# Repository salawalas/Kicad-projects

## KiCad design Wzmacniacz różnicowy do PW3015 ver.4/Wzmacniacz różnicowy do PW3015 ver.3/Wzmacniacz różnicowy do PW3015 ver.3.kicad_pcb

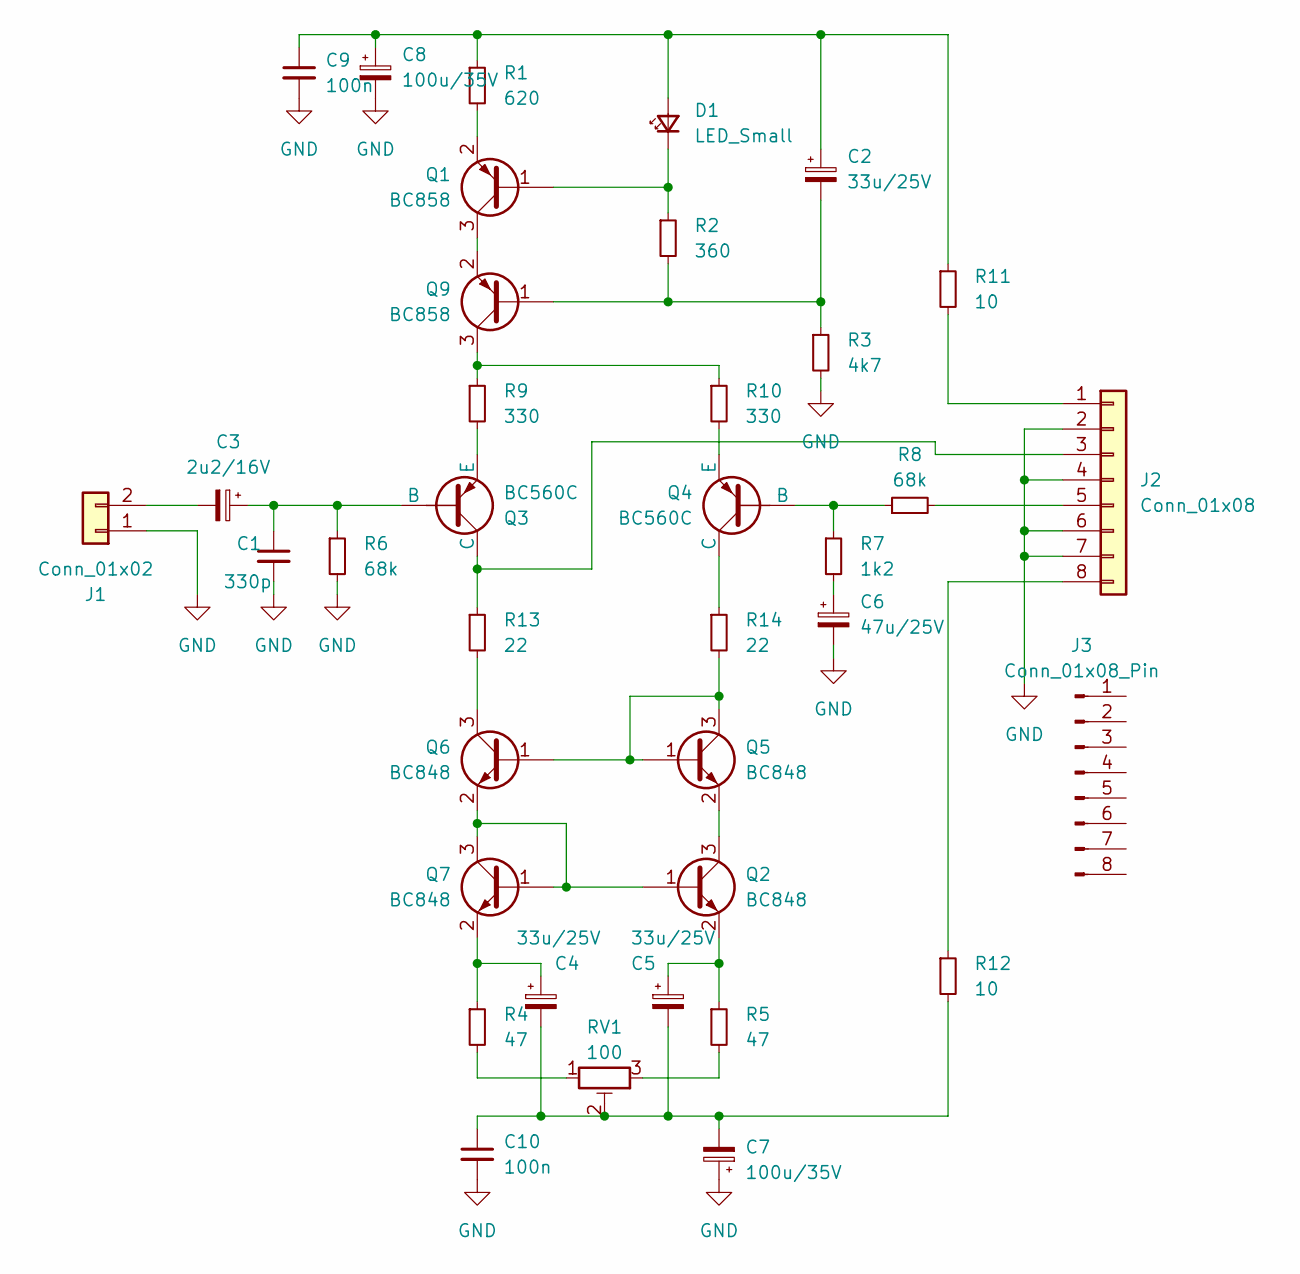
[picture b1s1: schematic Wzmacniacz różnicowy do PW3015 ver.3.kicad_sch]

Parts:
C1: 330p; C_Axial_L3.8mm_D2.6mm_P7.50mm_Horizontal
C2, C4, C5: 33u/25V; CP_Radial_Tantal_D5.5mm_P5.00mm
C3: 2u2/16V; CP_Radial_D5.0mm_P2.50mm
C6: 47u/25V; CP_Radial_D5.0mm_P2.50mm
C7, C8: 100u/35V; CP_Radial_D8.0mm_P5.00mm
C9, C10: 100n; C_0805_2012Metric_Pad1.18x1.45mm_HandSolder
D1: LED_Small; LED_D5.0mm
J1: Conn_01x02; JST_PH_B2B-PH-K_1x02_P2.00mm_Vertical
J2: Conn_01x08; PinHeader_1x08_P2.54mm_Horizontal
J3: Conn_01x08_Pin; PinHeader_1x08_P2.54mm_Vertical
Q1, Q9: BC858; SOT-23
Q2, Q5, Q6, Q7: BC848; SOT-23
Q3, Q4: BC560C; TO-92_Wide
R1: 620; R_1206_3216Metric_Pad1.30x1.75mm_HandSolder
R2: 360; R_1206_3216Metric_Pad1.30x1.75mm_HandSolder
R3: 4k7; R_1206_3216Metric_Pad1.30x1.75mm_HandSolder
R4, R5: 47; R_1206_3216Metric_Pad1.30x1.75mm_HandSolder
R6, R8: 68k; R_1206_3216Metric_Pad1.30x1.75mm_HandSolder
R7: 1k2; R_1206_3216Metric_Pad1.30x1.75mm_HandSolder
R9, R10: 330; R_1206_3216Metric_Pad1.30x1.75mm_HandSolder
R11, R12: 10; R_1206_3216Metric_Pad1.30x1.75mm_HandSolder
R13, R14: 22; R_1206_3216Metric_Pad1.30x1.75mm_HandSolder
RV1: 100; Potentiometer_Bourns_3296X_Horizontal

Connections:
GND: C1.2, C6.2, C7.1, C8.2, C9.2, C10.2, J1.1, J2.2, J2.4, J2.6, J2.7, R3.2, R6.2
unnamed: C6.1, R7.2
unnamed: C4.2, C5.2, C7.2, C10.1, R12.2, RV1.2
unnamed: C2.1, C8.1, C9.1, D1.2 (A), R1.1, R11.1
unnamed: D1.1 (K), Q1.1 (B), R2.1
unnamed: C3.2, J1.2
unnamed: J2.1, R11.2
unnamed: J2.3, Q3.1 (C), R13.1
unnamed: J2.5, R8.2
unnamed: J2.8, R12.1
unnamed: Q1.3 (C), Q9.2 (E)
unnamed: Q1.2 (E), R1.2
unnamed: Q2.1 (B), Q6.2 (E), Q7.1 (B), Q7.3 (C)
unnamed: Q2.3 (C), Q5.2 (E)
unnamed: C5.1, Q2.2 (E), R5.1
unnamed: C1.1, C3.1, Q3.2 (B), R6.1
unnamed: Q3.3 (E), R9.2
unnamed: Q4.2 (B), R7.1, R8.1
unnamed: Q4.1 (C), R14.1
unnamed: Q4.3 (E), R10.2
unnamed: Q5.1 (B), Q5.3 (C), Q6.1 (B), R14.2
unnamed: Q6.3 (C), R13.2
unnamed: C4.1, Q7.2 (E), R4.1
unnamed: C2.2, Q9.1 (B), R2.2, R3.1
unnamed: Q9.3 (C), R9.1, R10.1
unnamed: R4.2, RV1.1
unnamed: R5.2, RV1.3

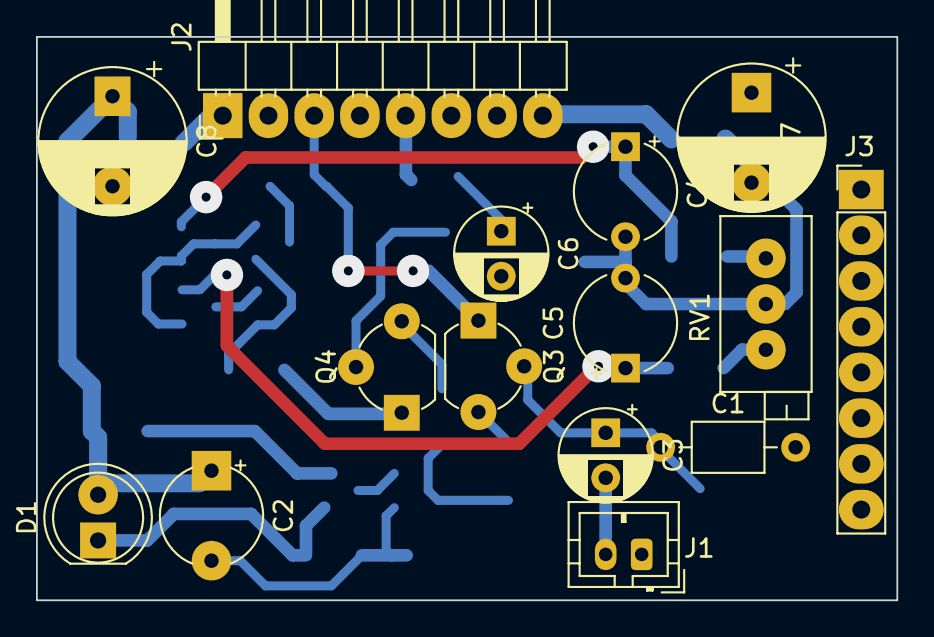
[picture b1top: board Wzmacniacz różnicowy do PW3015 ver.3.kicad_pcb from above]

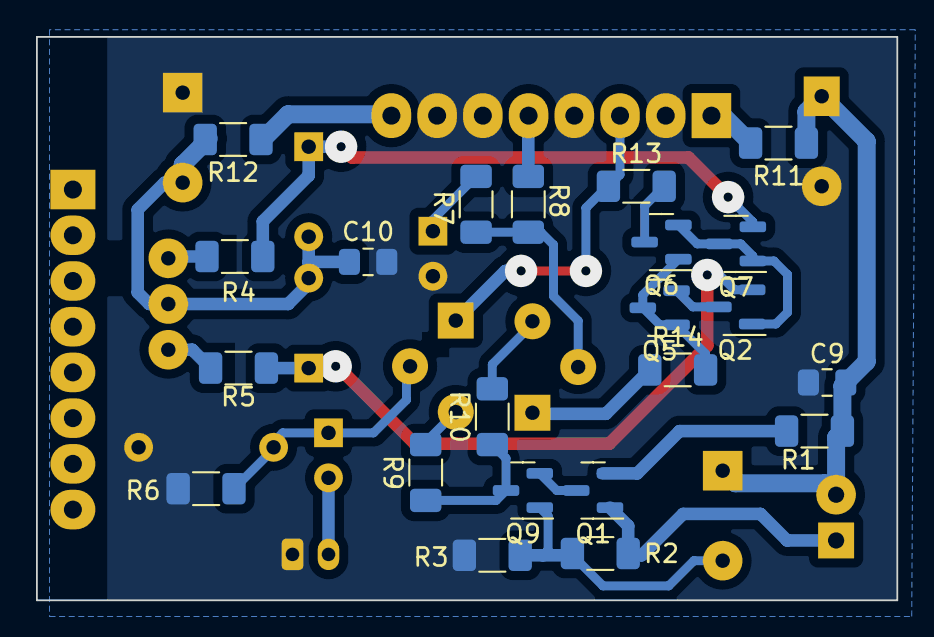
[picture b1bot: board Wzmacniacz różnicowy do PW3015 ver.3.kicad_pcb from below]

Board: 2 copper layers, 47.8 x 31.3 mm, 37 parts (22 on the bottom side), 27 nets.

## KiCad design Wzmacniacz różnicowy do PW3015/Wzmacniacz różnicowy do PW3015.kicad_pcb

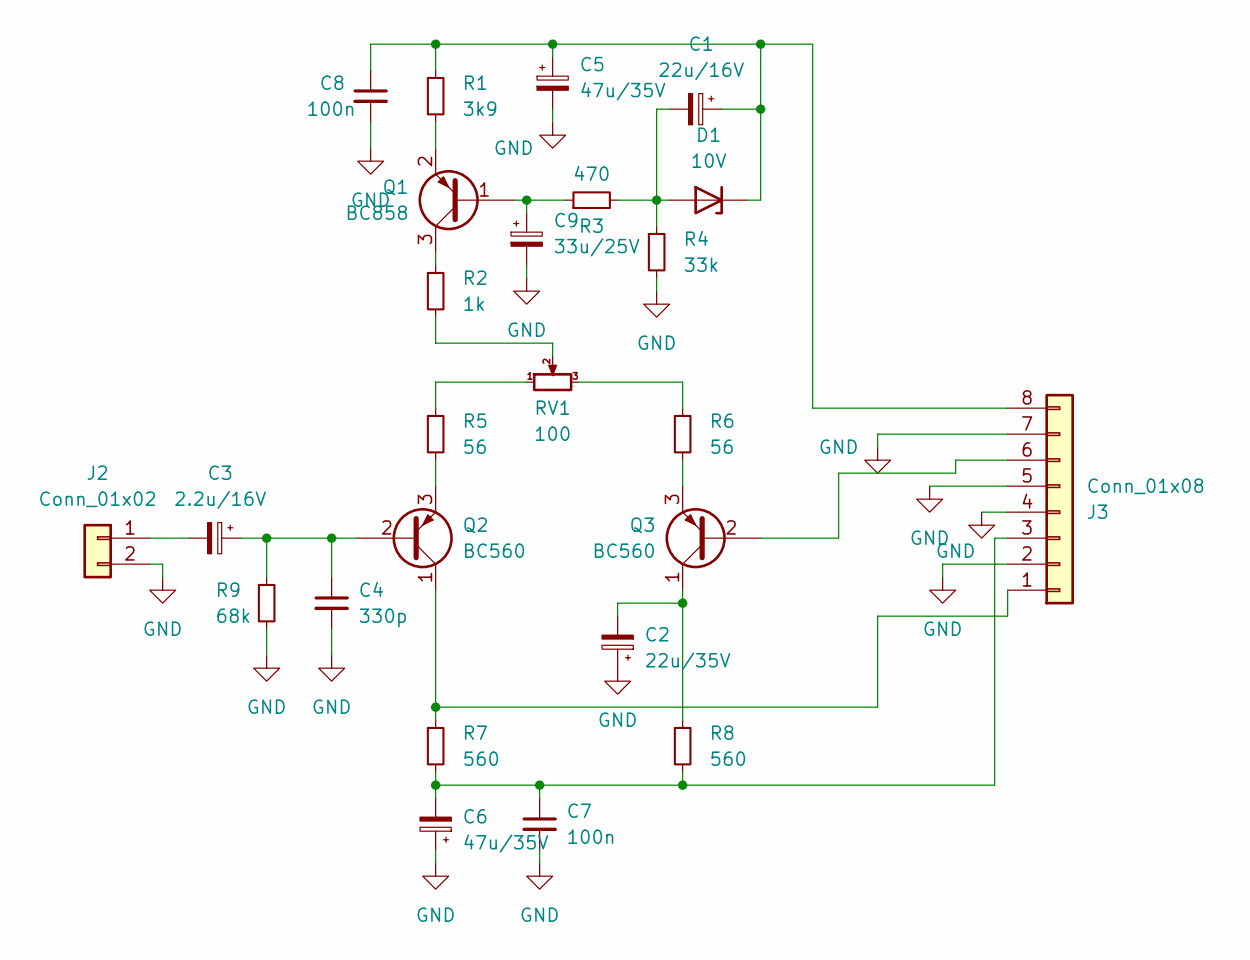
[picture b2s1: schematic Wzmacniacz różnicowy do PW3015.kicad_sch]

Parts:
C1: 22u/16V; CP_Radial_D5.0mm_P2.50mm
C2: 22u/35V; CP_Radial_D8.0mm_P3.80mm
C3: 2.2u/16V; CP_Radial_D5.0mm_P2.50mm
C4: 330p; C_Disc_D4.3mm_W1.9mm_P5.00mm
C5, C6: 47u/35V; CP_Radial_D10.0mm_P3.50mm
C7, C8: 100n; C_0805_2012Metric_Pad1.18x1.45mm_HandSolder
C9: 33u/25V; CP_Radial_Tantal_D5.5mm_P5.00mm
D1: 10V; D_T-1_P5.08mm_Horizontal
J2: Conn_01x02; JST_EH_B2B-EH-A_1x02_P2.50mm_Vertical
J3: Conn_01x08; PinHeader_1x08_P2.54mm_Horizontal
Q1: BC858; SOT-23
Q2, Q3: BC560; TO-92L_Wide
R1: 3k9; R_1206_3216Metric_Pad1.30x1.75mm_HandSolder
R2: 1k; R_1206_3216Metric_Pad1.30x1.75mm_HandSolder
R3: 470; R_1206_3216Metric_Pad1.30x1.75mm_HandSolder
R4: 33k; R_1206_3216Metric_Pad1.30x1.75mm_HandSolder
R5, R6: 56; R_1206_3216Metric_Pad1.30x1.75mm_HandSolder
R7, R8: 560; R_1206_3216Metric_Pad1.30x1.75mm_HandSolder
R9: 68k; R_1206_3216Metric_Pad1.30x1.75mm_HandSolder
RV1: 100; Potentiometer_Bourns_3296W_Vertical

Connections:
GND: C2.1, C4.2, C5.2, C6.1, C7.2, C8.2, C9.2, J2.2, J3.2, J3.4, J3.5, J3.7, R4.2, R9.2
unnamed: C1.2, D1.2 (A), R3.2, R4.1
unnamed: C1.1, C5.1, C8.1, D1.1 (K), J3.8, R1.1
unnamed: C3.2, J2.1
unnamed: J3.1, Q2.1 (C), R7.1
unnamed: C6.2, C7.1, J3.3, R7.2, R8.2
unnamed: J3.6, Q3.2 (B)
unnamed: C9.1, Q1.1 (B), R3.1
unnamed: Q1.3 (C), R2.1
unnamed: Q1.2 (E), R1.2
unnamed: C3.1, C4.1, Q2.2 (B), R9.1
unnamed: Q2.3 (E), R5.2
unnamed: C2.2, Q3.1 (C), R8.1
unnamed: Q3.3 (E), R6.2
unnamed: R2.2, RV1.2
unnamed: R5.1, RV1.1
unnamed: R6.1, RV1.3

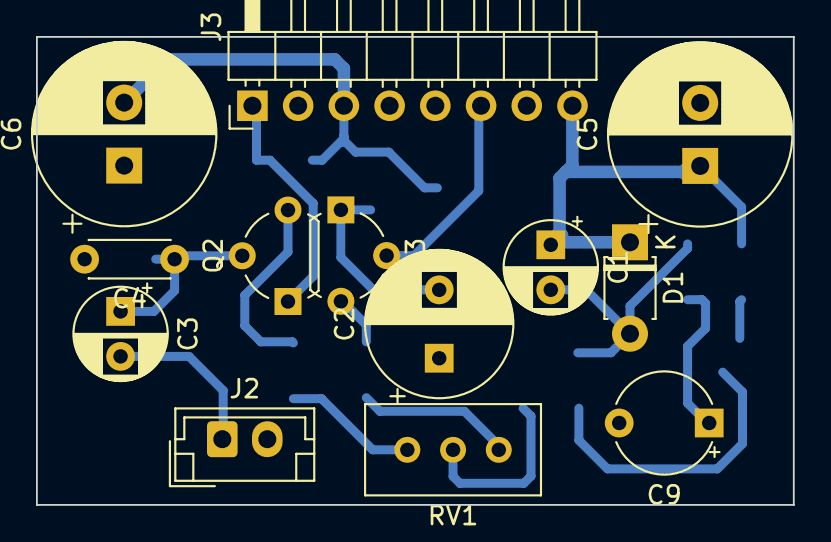
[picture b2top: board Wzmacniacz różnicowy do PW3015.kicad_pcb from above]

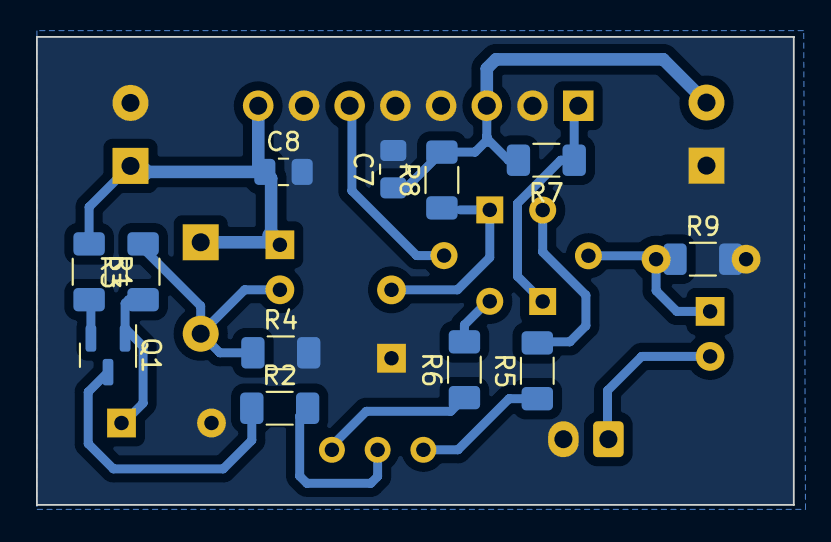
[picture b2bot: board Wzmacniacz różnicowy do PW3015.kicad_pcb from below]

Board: 2 copper layers, 42.1 x 26.0 mm, 25 parts (12 on the bottom side), 17 nets.

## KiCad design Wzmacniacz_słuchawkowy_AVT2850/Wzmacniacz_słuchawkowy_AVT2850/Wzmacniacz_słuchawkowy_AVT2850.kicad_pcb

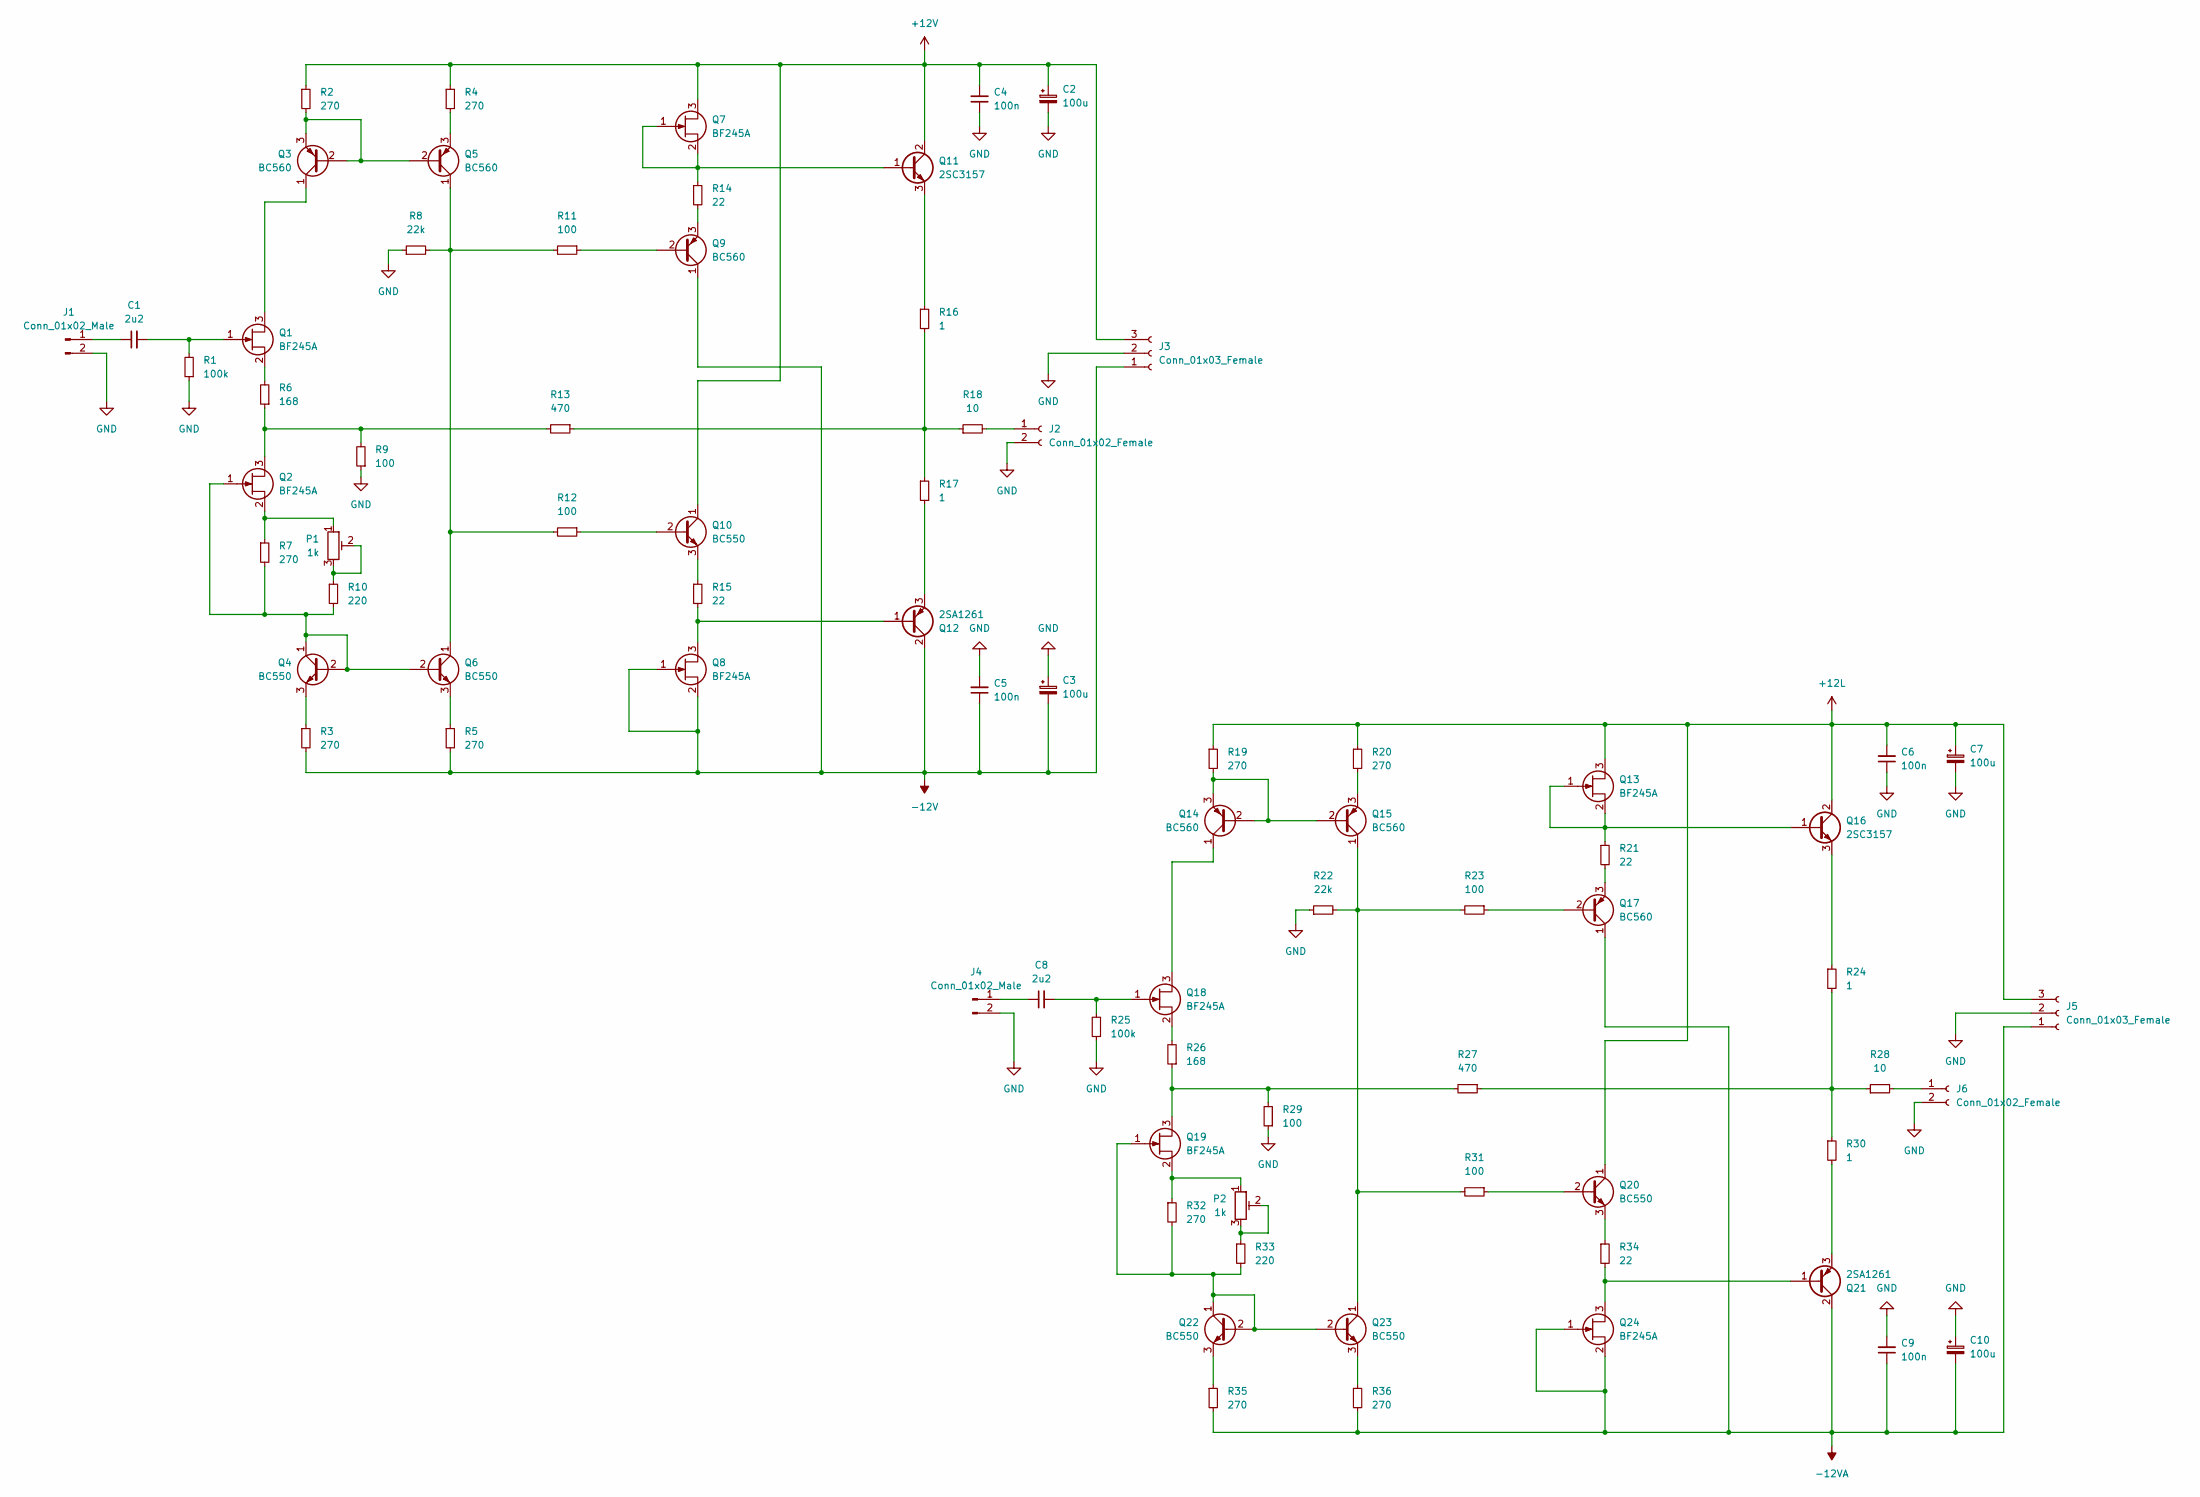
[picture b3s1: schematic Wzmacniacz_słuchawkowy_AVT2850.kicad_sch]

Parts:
C1, C8: 2u2; C_Rect_L11.0mm_W5.1mm_P10.00mm_MKT
C2, C3, C7, C10: 100u; CP_Radial_D8.0mm_P3.50mm
C4, C5, C6, C9: 100n; C_Axial_L3.8mm_D2.6mm_P10.00mm_Horizontal
J1, J4: Conn_01x02_Male; JST_EH_S2B-EH_1x02_P2.50mm_Horizontal
J2, J6: Conn_01x02_Female; JST_EH_B2B-EH-A_1x02_P2.50mm_Vertical
J3, J5: Conn_01x03_Female; JST_EH_S3B-EH_1x03_P2.50mm_Horizontal
P1, P2: 1k; Potentiometer_Bourns_3266Y_Vertical
Q1, Q2, Q7, Q8, Q13, Q18, Q19, Q24: BF245A; TO-92
Q3, Q5, Q9, Q14, Q15, Q17: BC560; TO-92
Q4, Q6, Q10, Q20, Q22, Q23: BC550; TO-92
Q11, Q16: 2SC3157; TO-220-3_Vertical
Q12, Q21: 2SA1261; TO-220-3_Vertical
R1, R25: 100k; R_Axial_DIN0207_L6.3mm_D2.5mm_P10.16mm_Horizontal
R2, R3, R4, R5, R7, R19, R20, R32, R35, R36: 270; R_Axial_DIN0207_L6.3mm_D2.5mm_P10.16mm_Horizontal
R6, R26: 168; R_Axial_DIN0207_L6.3mm_D2.5mm_P10.16mm_Horizontal
R8, R22: 22k; R_Axial_DIN0207_L6.3mm_D2.5mm_P10.16mm_Horizontal
R9, R11, R12, R23, R29, R31: 100; R_Axial_DIN0207_L6.3mm_D2.5mm_P10.16mm_Horizontal
R10, R33: 220; R_Axial_DIN0207_L6.3mm_D2.5mm_P10.16mm_Horizontal
R13, R27: 470; R_Axial_DIN0207_L6.3mm_D2.5mm_P10.16mm_Horizontal
R14, R15, R21, R34: 22; R_Axial_DIN0207_L6.3mm_D2.5mm_P10.16mm_Horizontal
R16, R17, R24, R30: 1; R_Axial_DIN0207_L6.3mm_D2.5mm_P10.16mm_Horizontal
R18, R28: 10; R_Axial_DIN0207_L6.3mm_D2.5mm_P10.16mm_Horizontal

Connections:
+12L: C6.2, C7.1, J5.3, Q13.3 (D), Q16.2 (C), Q20.1 (C), R19.1, R20.1
+12V: C2.1, C4.2, J3.3, Q7.3 (D), Q10.1 (C), Q11.2 (C), R2.1, R4.1
-12V: C3.2, C5.1, J3.1, Q8.1 (G), Q8.2 (S), Q9.1 (C), Q12.2 (C), R3.2, R5.2
-12VA: C9.1, C10.2, J5.1, Q17.1 (C), Q21.2 (C), Q24.1 (G), Q24.2 (S), R35.2, R36.2
GND: C2.2, C3.1, C4.1, C5.2, C6.1, C7.2, C9.2, C10.1, J1.2, J2.2, J3.2, J4.2, J5.2, J6.2, R1.1, R8.1, R9.1, R22.1, R25.1, R29.1
unnamed: C1.1, J1.1
unnamed: C1.2, Q1.1 (G), R1.2
unnamed: C8.1, J4.1
unnamed: C8.2, Q18.1 (G), R25.2
unnamed: J2.1, R18.2
unnamed: J6.1, R28.2
unnamed: P1.1, Q2.2 (S), R7.1
unnamed: P1.2, P1.3, R10.1
unnamed: P2.1, Q19.2 (S), R32.1
unnamed: P2.2, P2.3, R33.1
unnamed: Q1.2 (S), R6.2
unnamed: Q1.3 (D), Q3.1 (C)
unnamed: Q2.1 (G), Q4.1 (C), Q4.2 (B), Q6.2 (B), R7.2, R10.2
unnamed: Q2.3 (D), R6.1, R9.2, R13.2
unnamed: Q3.2 (B), Q3.3 (E), Q5.2 (B), R2.2
unnamed: Q4.3 (E), R3.1
unnamed: Q5.1 (C), Q6.1 (C), R8.2, R11.2, R12.2
unnamed: Q5.3 (E), R4.2
unnamed: Q6.3 (E), R5.1
unnamed: Q9.2 (B), R11.1
unnamed: Q9.3 (E), R14.2
unnamed: Q10.2 (B), R12.1
unnamed: Q10.3 (E), R15.1
unnamed: Q7.1 (G), Q7.2 (S), Q11.1 (B), R14.1
unnamed: Q11.3 (E), R16.1
unnamed: Q8.3 (D), Q12.1 (B), R15.2
unnamed: Q12.3 (E), R17.2
unnamed: Q13.1 (G), Q13.2 (S), Q16.1 (B), R21.1
unnamed: Q14.1 (C), Q18.3 (D)
unnamed: Q14.2 (B), Q14.3 (E), Q15.2 (B), R19.2
unnamed: Q15.1 (C), Q23.1 (C), R22.2, R23.2, R31.2
unnamed: Q15.3 (E), R20.2
unnamed: Q16.3 (E), R24.1
unnamed: Q17.2 (B), R23.1
unnamed: Q17.3 (E), R21.2
unnamed: Q18.2 (S), R26.2
unnamed: Q19.1 (G), Q22.1 (C), Q22.2 (B), Q23.2 (B), R32.2, R33.2
unnamed: Q19.3 (D), R26.1, R27.2, R29.2
unnamed: Q20.2 (B), R31.1
unnamed: Q20.3 (E), R34.1
unnamed: Q21.1 (B), Q24.3 (D), R34.2
unnamed: Q21.3 (E), R30.2
unnamed: Q22.3 (E), R35.1
unnamed: Q23.3 (E), R36.1
unnamed: R13.1, R16.2, R17.1, R18.1
unnamed: R24.2, R27.1, R28.1, R30.1

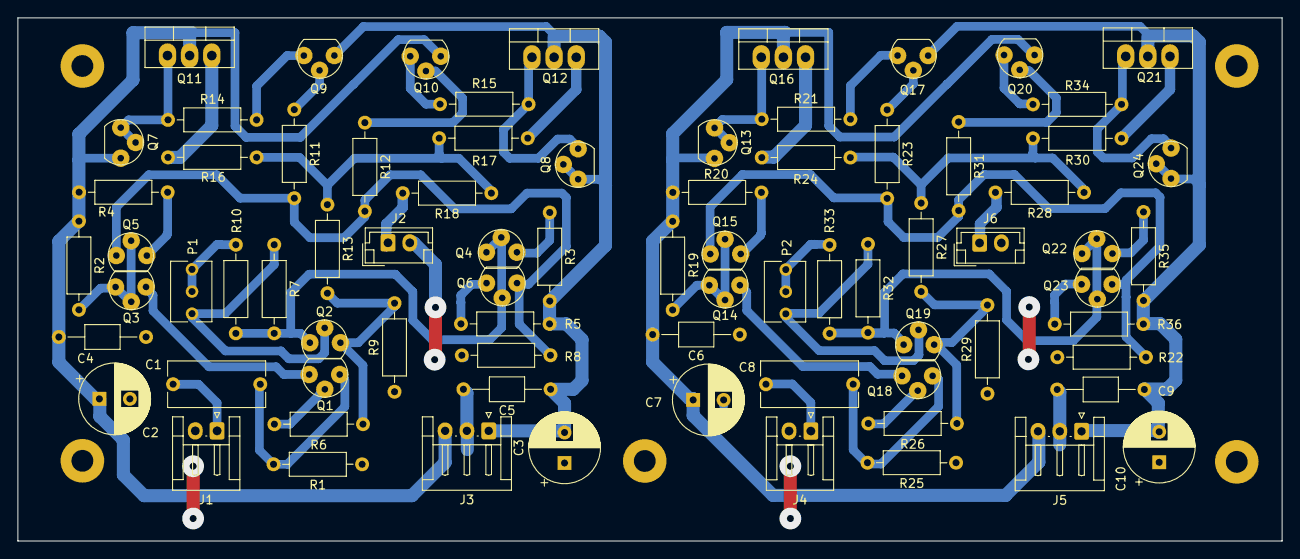
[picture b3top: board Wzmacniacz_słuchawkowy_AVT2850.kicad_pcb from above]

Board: 2 copper layers, 145.0 x 60.0 mm, 78 parts (0 on the bottom side), 51 nets.

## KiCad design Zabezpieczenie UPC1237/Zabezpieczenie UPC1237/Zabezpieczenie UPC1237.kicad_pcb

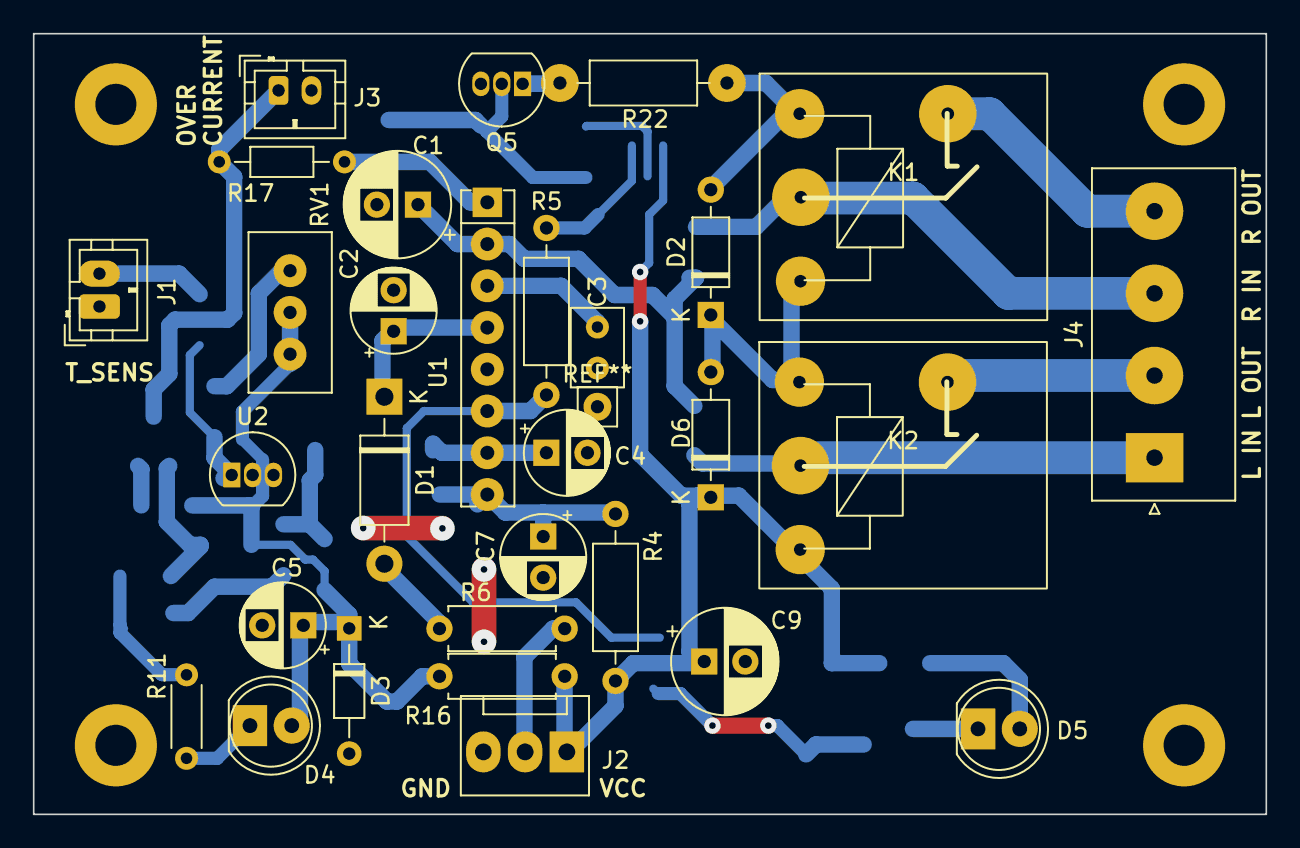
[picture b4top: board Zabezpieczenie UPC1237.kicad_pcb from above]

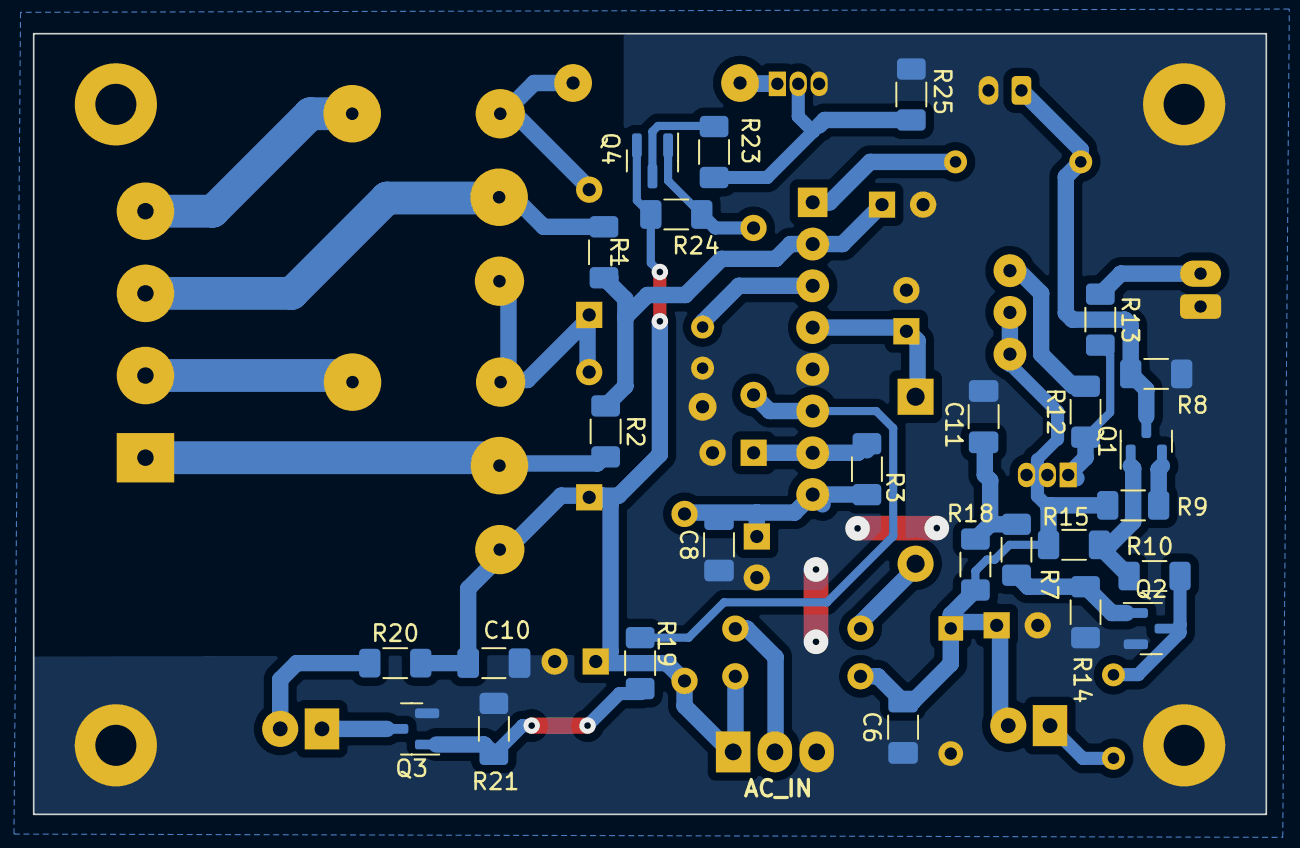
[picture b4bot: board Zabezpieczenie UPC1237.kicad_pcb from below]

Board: 2 copper layers, 75.0 x 47.5 mm, 56 parts (26 on the bottom side), 35 nets.

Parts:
C1: 330u/10/16V; CP_Radial_D6.3mm_P2.50mm
C2, C4: 4.7u/10/16V; CP_Radial_D5.0mm_P2.50mm
C3: 22n; C_Rect_L4.6mm_W3.0mm_P2.50mm_MKS02_FKP02
C5: 47u/16V; CP_Radial_D5.0mm_P2.50mm
C6, C8, C10, C11: 0.1u; C_1206_3216Metric_Pad1.33x1.80mm_HandSolder
C7: 47u/10/16; CP_Radial_D5.0mm_P2.50mm
C9: 100u/40V; CP_Radial_D6.3mm_P2.50mm
D1: 1N4007; D_DO-41_SOD81_P10.16mm_Horizontal
D2, D6: 1N4148; D_DO-35_SOD27_P7.62mm_Horizontal
D3: 12V; D_DO-34_SOD68_P7.62mm_Horizontal
D4, D5: LED_Small; LED_D5.0mm
J1, J3: Conn_01x02; JST_PH_B2B-PH-K_1x02_P2.00mm_Vertical
J2: Conn_01x03; FanPinHeader_1x03_P2.54mm_Vertical
J4: Conn_01x04_Pin; JST_NV_B04P-NV_1x04_P5.00mm_Vertical
K1, K2: Relay_SPST-NO; Relay_Hongfa_HF3FF
Q1, Q4: BC858; SOT-23
Q2, Q3: BC847; SOT-23
Q5: BC337; TO-92_Inline
R1, R2, R3: 56k; R_1206_3216Metric_Pad1.30x1.75mm_HandSolder
R4: 9k1; R_Axial_DIN0207_L6.3mm_D2.5mm_P10.16mm_Horizontal
R5: 47k; R_Axial_DIN0207_L6.3mm_D2.5mm_P10.16mm_Horizontal
R6: 12k; R_Axial_DIN0207_L6.3mm_D2.5mm_P7.62mm_Horizontal
R7, R14, R15: 4k7; R_1206_3216Metric_Pad1.30x1.75mm_HandSolder
R8: 2k7; R_1206_3216Metric_Pad1.30x1.75mm_HandSolder
R9: 3k9; R_1206_3216Metric_Pad1.30x1.75mm_HandSolder
R10: 1k; R_1206_3216Metric_Pad1.30x1.75mm_HandSolder
R11: 4k7; R_Axial_DIN0204_L3.6mm_D1.6mm_P5.08mm_Horizontal
R12: 3k; R_1206_3216Metric_Pad1.30x1.75mm_HandSolder
R13: 200; R_1206_3216Metric_Pad1.30x1.75mm_HandSolder
R16: 2k; R_Axial_DIN0207_L6.3mm_D2.5mm_P7.62mm_Horizontal
R17: 27k; R_Axial_DIN0204_L3.6mm_D1.6mm_P7.62mm_Horizontal
R18: 6k8; R_1206_3216Metric_Pad1.30x1.75mm_HandSolder
R19, R21, R23, R24, R25: 47k; R_1206_3216Metric_Pad1.30x1.75mm_HandSolder
R20: 10k; R_1206_3216Metric_Pad1.30x1.75mm_HandSolder
R22: 56; R_Axial_DIN0207_L6.3mm_D2.5mm_P10.16mm_Horizontal
RV1: 2k; Potentiometer_Bourns_3296W_Vertical
U1: UP1237; SIP-8_19x3mm_P2.54mm
U2: TL431LP; TO-92_Inline

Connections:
/INPUT_AC: J2.2, R6.1
/INPUT_L: J4.1, K2.13, R2.2
/INPUT_R: J4.3, K1.13, R1.2
/OUPUT_L: J4.2, K2.14
/OUPUT_R: J4.4, K1.14
/OVERLOAD_DET: R17.1, U1.1 (Overload_Detector)
/VCC: C9.1, C10.2, D6.1 (K), J2.1, K2.A2, Q4.2 (E), R4.1, R16.1, R20.2, R24.2
GND: C1.2, C2.2, C3.2, C4.2, C5.2, C6.2, C7.2, C8.1, C9.2, C10.1, C11.2, D3.2 (A), J1.1, J2.3, J3.2, Q2.2 (E), Q3.2 (E), Q5.3 (E), R8.1, R14.1, R21.1, R25.2, U1.5 (GND), U2.2 (A)
unnamed: D1.2 (A), R6.2
unnamed: C2.1, D1.1 (K), U1.4 (AC_OFF_Detector)
unnamed: D2.2 (A), K1.A1, R22.2
unnamed: D2.1 (K), D6.2 (A), K1.A2, K2.A1
unnamed: C5.1, C6.1, D3.1 (K), D4.2 (A), R9.2, R15.2, R16.2, R18.1, RV1.2, RV1.3
unnamed: D4.1 (K), R11.2
unnamed: D5.2 (A), R20.1
unnamed: D5.1 (K), Q3.3 (C)
unnamed: J1.2, R13.1
unnamed: J3.1, Q1.3 (C), R8.2, R17.2
unnamed: Q1.1 (B), R10.2, R15.1
unnamed: Q1.2 (E), R9.1
unnamed: Q2.1 (B), R7.2, R14.2
unnamed: Q2.3 (C), R10.1, R11.1
unnamed: Q3.1 (B), R19.2, R21.2
unnamed: Q4.1 (B), R5.2, R24.1
unnamed: Q4.3 (C), R23.2
unnamed: Q5.2 (B), R23.1, R25.1
unnamed: Q5.1 (C), R22.1
unnamed: R12.2, RV1.1
unnamed: C7.1, C8.2, R3.2, R4.2, U1.8 (+VCC)
unnamed: C3.1, U1.3 (Latch/Automat_Reset)
unnamed: C1.1, R1.1, R2.1, U1.2 (Output_Offset_Det.)
unnamed: R5.1, R19.1, U1.6 (Output_Relay_Driver)
unnamed: C4.1, R3.1, U1.7 (VCC_ON_Mute)
unnamed: C11.1, R7.1, R18.2, U2.3 (K)
unnamed: R12.1, R13.2, U2.1 (REF)

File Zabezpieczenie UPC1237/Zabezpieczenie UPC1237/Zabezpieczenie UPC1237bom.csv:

Reference;Value;Footprint
C1;330u/10/16V;Capacitor_THT:CP_Radial_D6.3mm_P2.50mm
C2 C4;4.7u/10/16V;Capacitor_THT:CP_Radial_D5.0mm_P2.50mm
C3;22n;Capacitor_THT:C_Rect_L4.6mm_W3.0mm_P2.50mm_MKS02_FKP02
C5;47u/16V;Capacitor_THT:CP_Radial_D5.0mm_P2.50mm
C6 C8 C10 C11;0.1u;Capacitor_SMD:C_1206_3216Metric_Pad1.33x1.80mm_HandSolder
C7;47u/10/16;Capacitor_THT:CP_Radial_D5.0mm_P2.50mm
C9;100u/40V;Capacitor_THT:CP_Radial_D6.3mm_P2.50mm
D1;1N4007;Diode_THT:D_DO-41_SOD81_P10.16mm_Horizontal
D2 D6;1N4148;Diode_THT:D_DO-35_SOD27_P7.62mm_Horizontal
D3;12V;Diode_THT:D_DO-34_SOD68_P7.62mm_Horizontal
D4 D5;LED_Small;LED_THT:LED_D5.0mm
J1 J3;Conn_01x02;Connector_JST:JST_PH_B2B-PH-K_1x02_P2.00mm_Vertical
J2;Conn_01x03;Connector:FanPinHeader_1x03_P2.54mm_Vertical
J4;Conn_01x04_Pin;Connector_JST:JST_NV_B04P-NV_1x04_P5.00mm_Vertical
K1 K2;Relay_SPST-NO;Relay:Relay_Hongfa_HF3FF
Q1 Q4;BC858;Package_TO_SOT_SMD:SOT-23
Q2 Q3;BC847;Package_TO_SOT_SMD:SOT-23
Q5;BC337;Package_TO_SOT_THT:TO-92_Inline
R1 R2 R3;56k;Resistor_SMD:R_1206_3216Metric_Pad1.30x1.75mm_HandSolder
R4;9k1;Resistor_THT:R_Axial_DIN0207_L6.3mm_D2.5mm_P10.16mm_Horizontal
R5;47k;Resistor_THT:R_Axial_DIN0207_L6.3mm_D2.5mm_P10.16mm_Horizontal
R6;12k;Resistor_THT:R_Axial_DIN0207_L6.3mm_D2.5mm_P7.62mm_Horizontal
R7 R14 R15;4k7;Resistor_SMD:R_1206_3216Metric_Pad1.30x1.75mm_HandSolder
R8;2k7;Resistor_SMD:R_1206_3216Metric_Pad1.30x1.75mm_HandSolder
R9;3k9;Resistor_SMD:R_1206_3216Metric_Pad1.30x1.75mm_HandSolder
R10;1k;Resistor_SMD:R_1206_3216Metric_Pad1.30x1.75mm_HandSolder
R11;4k7;Resistor_THT:R_Axial_DIN0204_L3.6mm_D1.6mm_P5.08mm_Horizontal
R12;3k;Resistor_SMD:R_1206_3216Metric_Pad1.30x1.75mm_HandSolder
R13;200;Resistor_SMD:R_1206_3216Metric_Pad1.30x1.75mm_HandSolder
R16;2k;Resistor_THT:R_Axial_DIN0207_L6.3mm_D2.5mm_P7.62mm_Horizontal
R17;27k;Resistor_THT:R_Axial_DIN0204_L3.6mm_D1.6mm_P7.62mm_Horizontal
R18;6k8;Resistor_SMD:R_1206_3216Metric_Pad1.30x1.75mm_HandSolder
R19 R21 R23 R24 R25;47k;Resistor_SMD:R_1206_3216Metric_Pad1.30x1.75mm_HandSolder
R20;10k;Resistor_SMD:R_1206_3216Metric_Pad1.30x1.75mm_HandSolder
R22;56;Resistor_THT:R_Axial_DIN0207_L6.3mm_D2.5mm_P10.16mm_Horizontal
RV1;2k;Potentiometer_THT:Potentiometer_Bourns_3296W_Vertical
U1;UP1237;Package_SIP:SIP-8_19x3mm_P2.54mm
U2;TL431LP;Package_TO_SOT_THT:TO-92_Wide

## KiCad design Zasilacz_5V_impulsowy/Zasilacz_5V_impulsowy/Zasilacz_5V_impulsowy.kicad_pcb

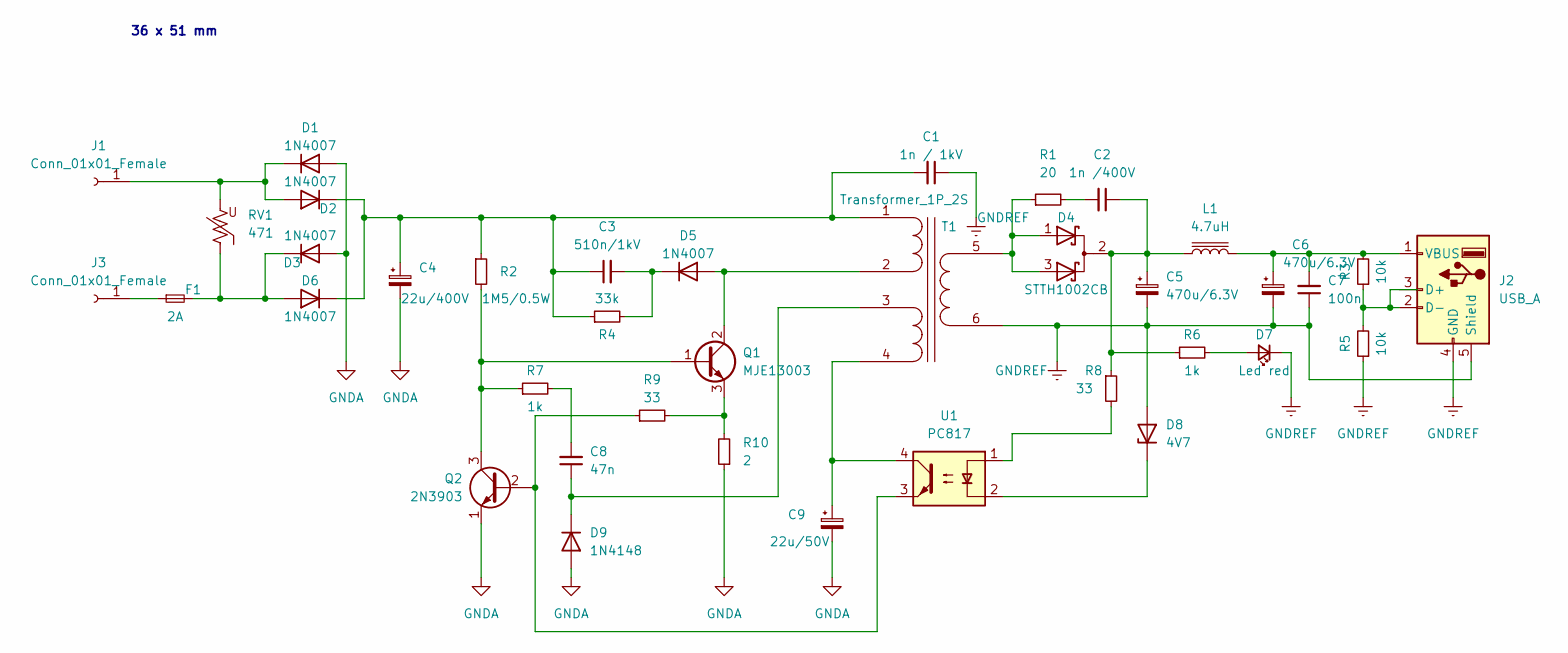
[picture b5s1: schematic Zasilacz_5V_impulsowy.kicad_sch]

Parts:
C1: 1n / 1kV; C_Disc_D7.5mm_W5.0mm_P10.00mm
C2: 1n /400V; C_1210_3225Metric
C3: 510n/1kV; C_Disc_D7.5mm_W5.0mm_P7.50mm
C4: 22u/400V; CP_Radial_D13.0mm_P5.00mm
C5, C6: 470u/6.3V; CP_Radial_D6.3mm_P2.50mm
C7: 100n; C_1206_3216Metric
C8: 47n; C_Disc_D4.7mm_W2.5mm_P5.00mm
C9: 22u/50V; CP_Radial_D5.0mm_P2.50mm
D1, D2, D3, D5, D6: 1N4007; D_DO-41_SOD81_P10.16mm_Horizontal
D4: STTH1002CB; TO-220-3_Vertical
D7: Led red; LED_Oval_W5.2mm_H3.8mm
D8: 4V7; D_DO-35_SOD27_P7.62mm_Horizontal
D9: 1N4148; D_DO-35_SOD27_P2.54mm_Vertical_KathodeUp
F1: 2A; R_Axial_DIN0309_L9.0mm_D3.2mm_P5.08mm_Vertical
J1, J3: Conn_01x01_Female; TestPoint_THTPad_D2.5mm_Drill1.2mm
J2: USB_A; USB_A_CONNFLY_DS1095-WNR0
L1: 4.7uH; L_Axial_L11.0mm_D4.5mm_P7.62mm_Vertical_Fastron_MECC
Q1: MJE13003; TO-126-3_Vertical
Q2: 2N3903; TO-92L
R1: 20; R_1210_3225Metric
R2: 1M5/0.5W; R_Axial_DIN0411_L9.9mm_D3.6mm_P7.62mm_Vertical
R3, R5: 10k; R_0805_2012Metric
R4: 33k; R_Axial_DIN0411_L9.9mm_D3.6mm_P7.62mm_Vertical
R6: 1k; R_0805_2012Metric
R7: 1k; R_1206_3216Metric
R8: 33; R_Axial_DIN0204_L3.6mm_D1.6mm_P5.08mm_Horizontal
R9: 33; R_0805_2012Metric
R10: 2; R_Axial_DIN0411_L9.9mm_D3.6mm_P5.08mm_Vertical
RV1: 471; RV_Disc_D12mm_W4.5mm_P7.5mm
T1: Transformer_1P_2S; Transformer_EE16_7.15_4.8
U1: PC817; DIP-4_W7.62mm

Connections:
GNDA: C4.2, C9.2, D1.2 (A), D3.2 (A), D9.2 (A), Q2.1 (E), R10.1
GNDREF: C1.1, C5.2, C6.2, C7.1, D7.1 (K), D8.2 (A), J2.4 (GND), J2.5 (Shield), R5.1, T1.6 (AB)
unnamed: C1.2, C3.1, C4.1, D2.1 (K), D6.1 (K), R2.1, R4.1, T1.1 (SA)
unnamed: C2.1, C5.1, D4.2 (A), L1.1, R6.1, R8.1
unnamed: C2.2, R1.2
unnamed: C3.2, D5.1 (K), R4.2
unnamed: C6.1, C7.2, J2.1 (VBUS), L1.2, R3.2
unnamed: C8.1, D9.1 (K), T1.3 (SC)
unnamed: C8.2, R7.2
unnamed: C9.1, T1.4 (SD), U1.4
unnamed: D1.1 (K), D2.2 (A), J1.1, RV1.2
unnamed: D3.1 (K), D6.2 (A), F1.2, RV1.1
unnamed: D4.1 (K), D4.3 (K), R1.1, T1.5 (AA)
unnamed: D5.2 (A), Q1.2 (C), T1.2 (SB)
unnamed: D7.2 (A), R6.2
unnamed: D8.1 (K), U1.2
unnamed: F1.1, J3.1
unnamed: J2.2 (D-), R3.1, R5.2
unnamed: Q1.1 (B), Q2.3 (C), R2.2, R7.1
unnamed: Q1.3 (E), R9.2, R10.2
unnamed: Q2.2 (B), R9.1, U1.3
unnamed: R8.2, U1.1

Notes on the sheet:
36 x 51 mm

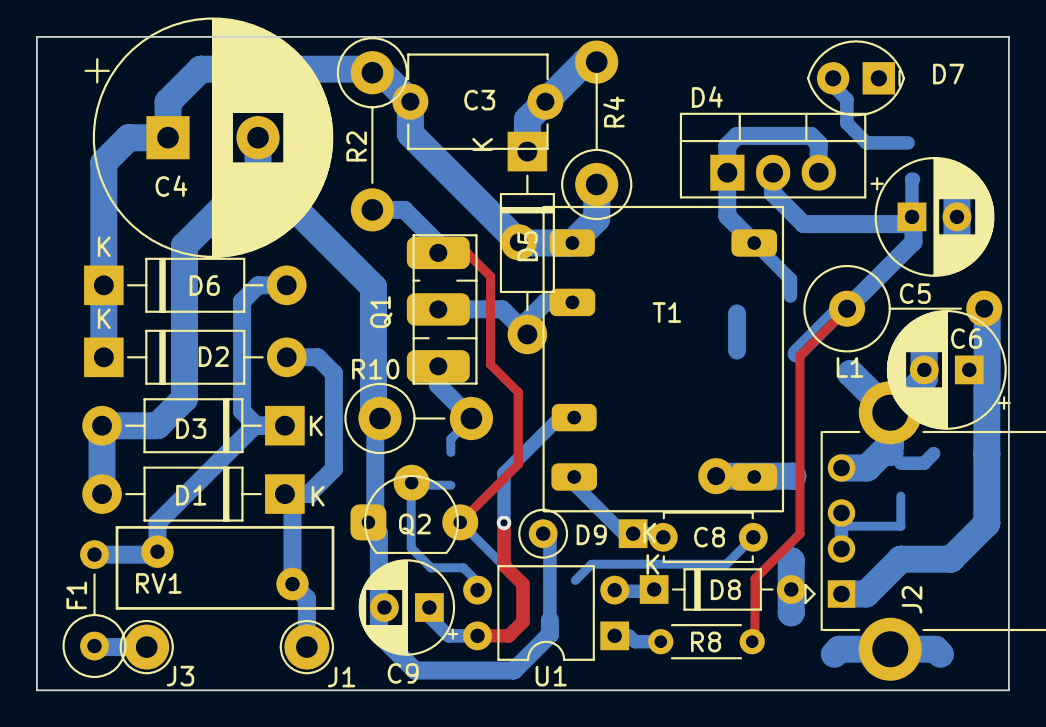
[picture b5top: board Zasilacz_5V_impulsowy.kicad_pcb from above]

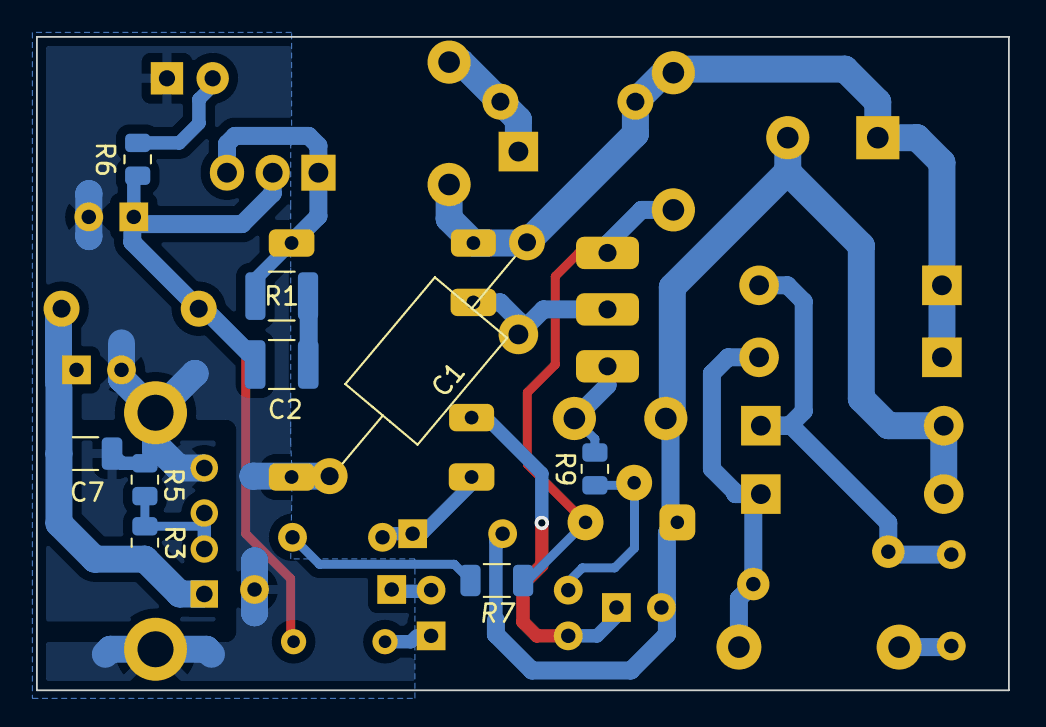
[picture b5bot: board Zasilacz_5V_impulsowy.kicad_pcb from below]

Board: 2 copper layers, 54.0 x 36.3 mm, 38 parts (9 on the bottom side), 22 nets.
